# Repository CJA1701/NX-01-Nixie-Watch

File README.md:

Nixie tube based watch I designed in 2024. For more info see the pdf presentation.

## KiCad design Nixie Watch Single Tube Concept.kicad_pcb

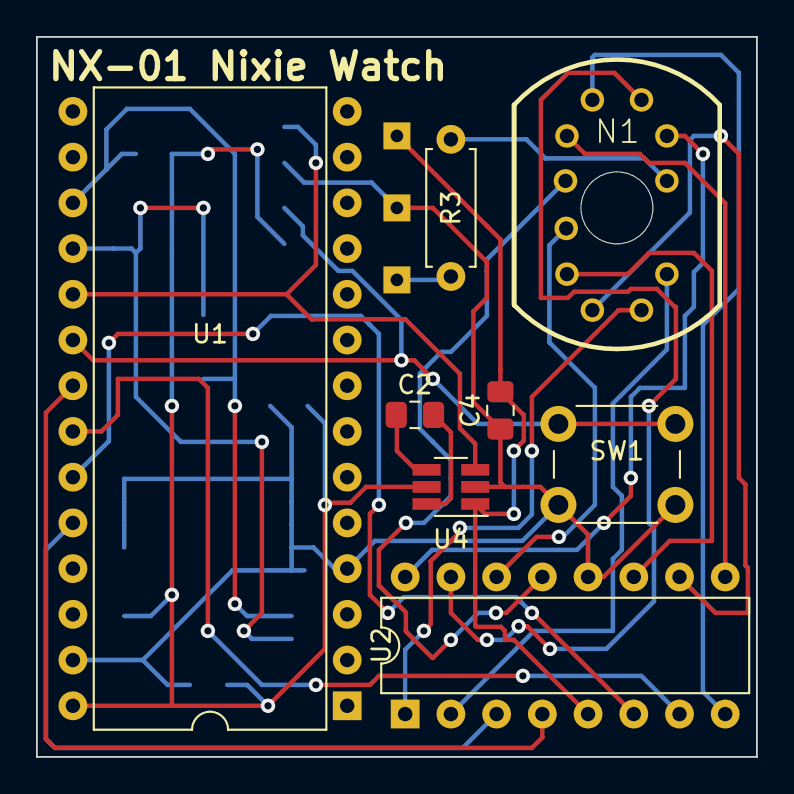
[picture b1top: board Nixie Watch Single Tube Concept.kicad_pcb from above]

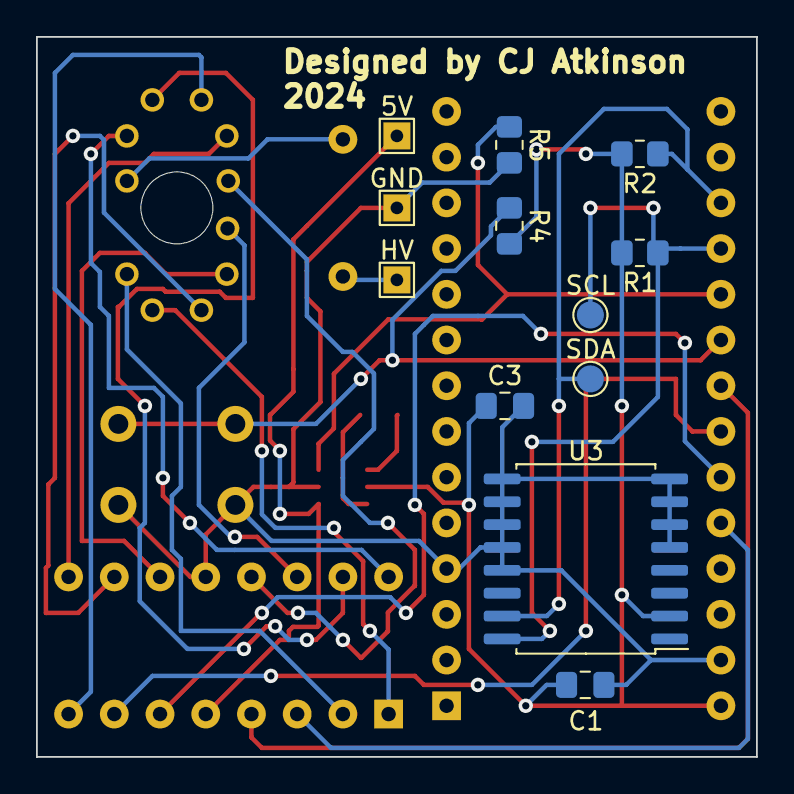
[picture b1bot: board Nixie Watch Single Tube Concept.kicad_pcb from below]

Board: 2 copper layers, 40.0 x 40.0 mm, 20 parts (12 on the bottom side), 25 nets.

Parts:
5V: 5V; TestPoint_THTPad_1.5x1.5mm_Drill0.7mm
C1: 0.1-1uF; C_0805_2012Metric_Pad1.18x1.45mm_HandSolder
C2: 1uF; C_0805_2012Metric_Pad1.18x1.45mm_HandSolder
C3, C4: 10uF; C_0805_2012Metric_Pad1.18x1.45mm_HandSolder
GND: GND; TestPoint_THTPad_1.5x1.5mm_Drill0.7mm
HV: HV; TestPoint_THTPad_1.5x1.5mm_Drill0.7mm
N1: IN-17; nixies-us-IN-17
R1, R2: 4.3K; R_0805_2012Metric_Pad1.20x1.40mm_HandSolder
R3: 39K 1/4W; R_Axial_DIN0207_L6.3mm_D2.5mm_P7.62mm_Horizontal
R4: 1K; R_0805_2012Metric_Pad1.20x1.40mm_HandSolder
R5: 100K; R_0805_2012Metric_Pad1.20x1.40mm_HandSolder
SCL: Conn_01x01_Pin; TestPoint_Pad_D1.5mm
SDA: Conn_01x01_Pin; TestPoint_Pad_D1.5mm
SW1: SW_Push; SW_PUSH_6mm_H4.3mm
U1: DIP-28_W15.24mm
U2: 74141; DIP-16_W7.62mm
U3: DS3231M; SOIC-16W_7.5x10.3mm_P1.27mm
U4: AP3602A; SOT-23-6_Handsoldering

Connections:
+BATT: C1.1, C3.1, R1.2, R2.2, R4.2, U1.28 (VBAT), U3.2 (VCC), U4.5 (VIN)
GND: C1.2, C3.2, C4.1, GND.1, R5.2, SW1.2, U1.4 (GND), U1.27 (GND), U2.12 (GND), U3.5 (GND), U3.6 (GND), U3.7 (GND), U3.8 (GND), U3.9 (GND), U3.10 (GND), U3.11 (GND), U3.12 (GND), U3.13 (GND), U4.2 (GND)
unnamed: 5V.1, C4.2, U2.5 (VCC), U4.1 (5VO)
unnamed: HV.1, R3.1
unnamed: N1.A, R3.2
unnamed: R1.1, SCL.1, U1.18 (SCL), U3.16 (SCL)
unnamed: R2.1, SDA.1, U1.17 (SDA), U3.15 (SDA)
unnamed: R5.1, U1.19 (D5), U4.3 (SHDN)
unnamed: R4.1, SW1.1, U1.20 (D7)
unnamed: U1.21 (D9), U2.4 (D)
unnamed: U1.22 (D10), U2.7 (C)
unnamed: U1.23 (D11), U2.6 (B)
unnamed: U1.24 (D12), U2.3 (A)
unnamed: N1.0, U2.16 (0)
unnamed: N1.1, U2.15 (1)
unnamed: N1.2, U2.8 (2)
unnamed: N1.3, U2.9 (3)
unnamed: N1.4, U2.13 (4)
unnamed: N1.5, U2.14 (5)
unnamed: N1.6, U2.11 (6)
unnamed: N1.7, U2.10 (7)
unnamed: N1.8, U2.1 (8)
unnamed: N1.9, U2.2 (9)
unnamed: C2.2, U4.6 (C+)
unnamed: C2.1, U4.4 (C-)

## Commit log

2024-04-28 PCB Files and Schematic
2024-04-28 Case Design V6.0
2024-06-06 Add files via upload
    Updated Firmware. Now with multiple function! Click once to show time, and twice to show date!
2024-06-06 Added presentation on design and construction.
    Presentation was originally made for my HS Physics final project.
2026-04-30 Software Version 3.0, With Sync Program
